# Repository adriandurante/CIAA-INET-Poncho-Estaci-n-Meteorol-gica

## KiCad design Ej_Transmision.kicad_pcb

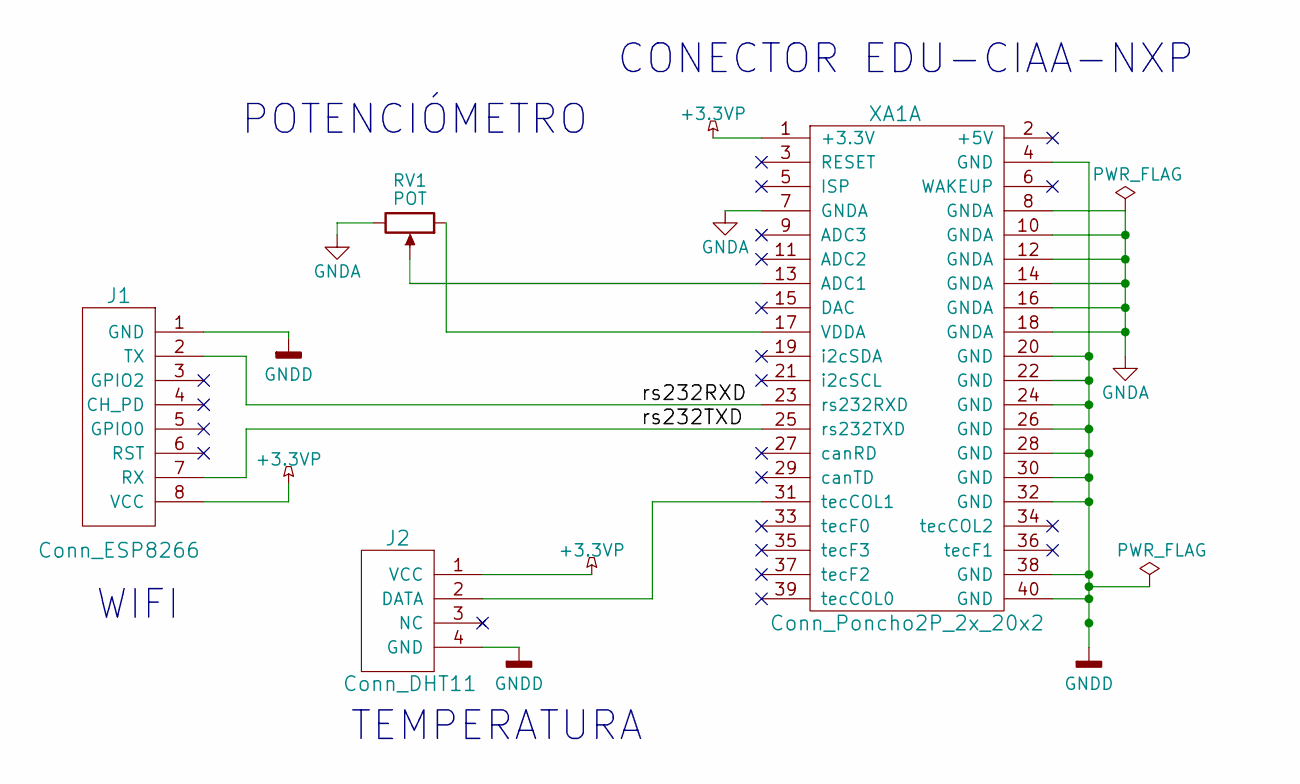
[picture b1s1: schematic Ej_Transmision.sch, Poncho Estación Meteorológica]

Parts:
J1: Conn_ESP8266; Conector_ESP01
J2: Conn_DHT11; Socket_Strip_Straight_1x04_Pitch2.54mm
RV1: POT; Potentiometer_Alps-RK16-single_largePads
XA1: Conn_Poncho2P_2x_20x2; Conn_Poncho_Derecha

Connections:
+3.3VP: J1.8 (VCC), J2.1 (VCC), XA1.1 (+3.3V)
/rs232RXD: J1.2 (TX), XA1.23 (rs232RXD)
/rs232TXD: J1.7 (RX), XA1.25 (rs232TXD)
GNDA: RV1.3, XA1.7 (GNDA), XA1.8 (GNDA), XA1.10 (GNDA), XA1.12 (GNDA), XA1.14 (GNDA), XA1.16 (GNDA), XA1.18 (GNDA)
GNDD: J1.1 (GND), J2.4 (GND), XA1.4 (GND), XA1.20 (GND), XA1.22 (GND), XA1.24 (GND), XA1.26 (GND), XA1.28 (GND), XA1.30 (GND), XA1.32 (GND), XA1.38 (GND), XA1.40 (GND)
unnamed: J2.2 (DATA), XA1.31 (tecCOL1)
unnamed: RV1.1, XA1.17 (VDDA)
unnamed: RV1.2, XA1.13 (ADC1)

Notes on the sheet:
TEMPERATURA
WIFI
POTENCIÓMETRO
CONECTOR EDU-CIAA-NXP

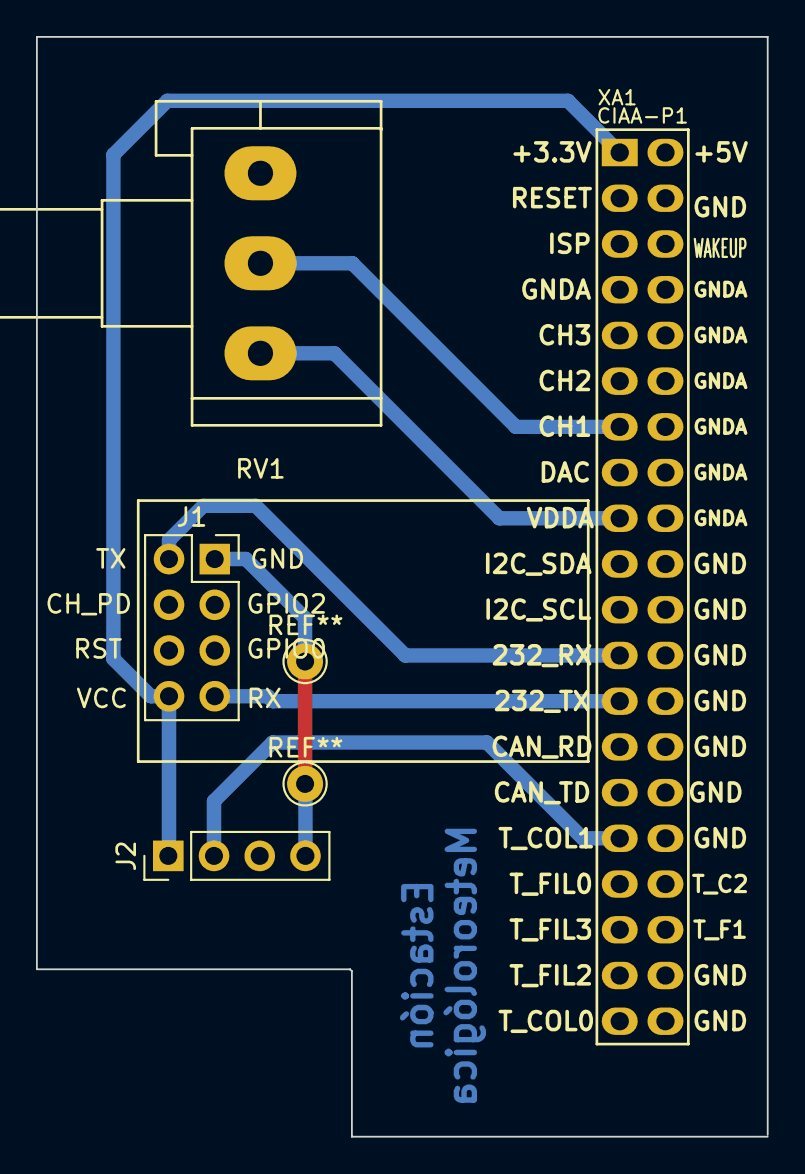
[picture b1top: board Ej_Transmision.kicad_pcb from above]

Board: 2 copper layers, 40.6 x 61.1 mm, 4 parts (0 on the bottom side), 8 nets.

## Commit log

2017-11-13 Versión 1
